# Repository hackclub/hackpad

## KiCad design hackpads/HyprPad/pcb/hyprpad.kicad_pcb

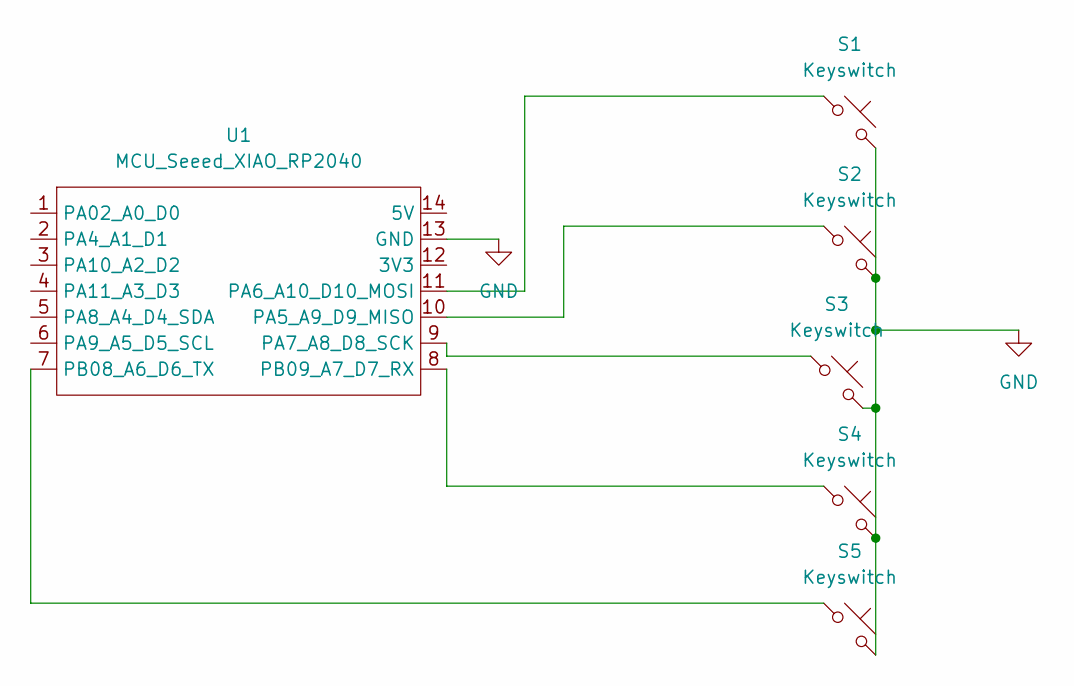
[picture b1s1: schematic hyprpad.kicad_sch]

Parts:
S1, S2, S3, S4, S5: Keyswitch; MX_PCB_1.00u
U1: MCU_Seeed_XIAO_RP2040; Seeed_XIAO_RP2040

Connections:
GND: S1.2, S2.2, S3.2, S4.2, S5.2, U1.13 (GND)
unnamed: S2.1, U1.10 (PA5_A9_D9_MISO)
unnamed: S1.1, U1.11 (PA6_A10_D10_MOSI)
unnamed: S3.1, U1.9 (PA7_A8_D8_SCK)
unnamed: S5.1, U1.7 (PB08_A6_D6_TX)
unnamed: S4.1, U1.8 (PB09_A7_D7_RX)

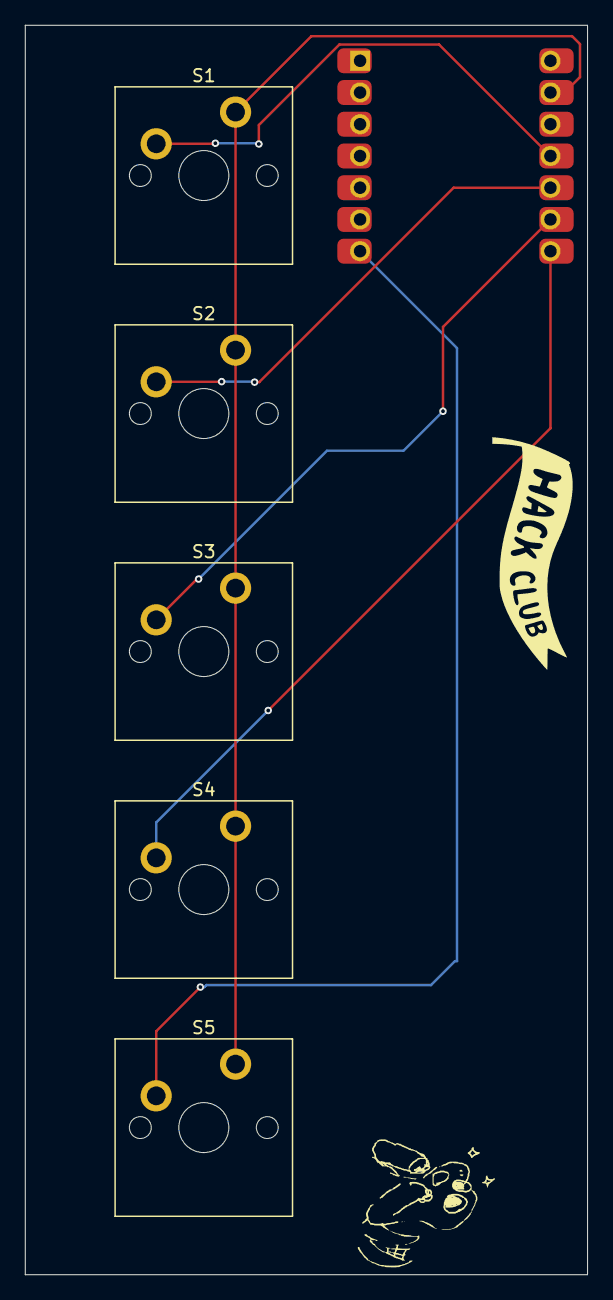
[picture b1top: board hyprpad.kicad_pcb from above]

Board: 2 copper layers, 45.0 x 100.0 mm, 6 parts (0 on the bottom side), 6 nets.

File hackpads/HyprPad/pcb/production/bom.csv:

Designator,Footprint,Quantity,Value,LCSC Part #
"S1, S2, S3, S4, S5",MX_PCB_1.00u,5,Keyswitch,
U1,Seeed_XIAO_RP2040,1,MCU_Seeed_XIAO_RP2040,

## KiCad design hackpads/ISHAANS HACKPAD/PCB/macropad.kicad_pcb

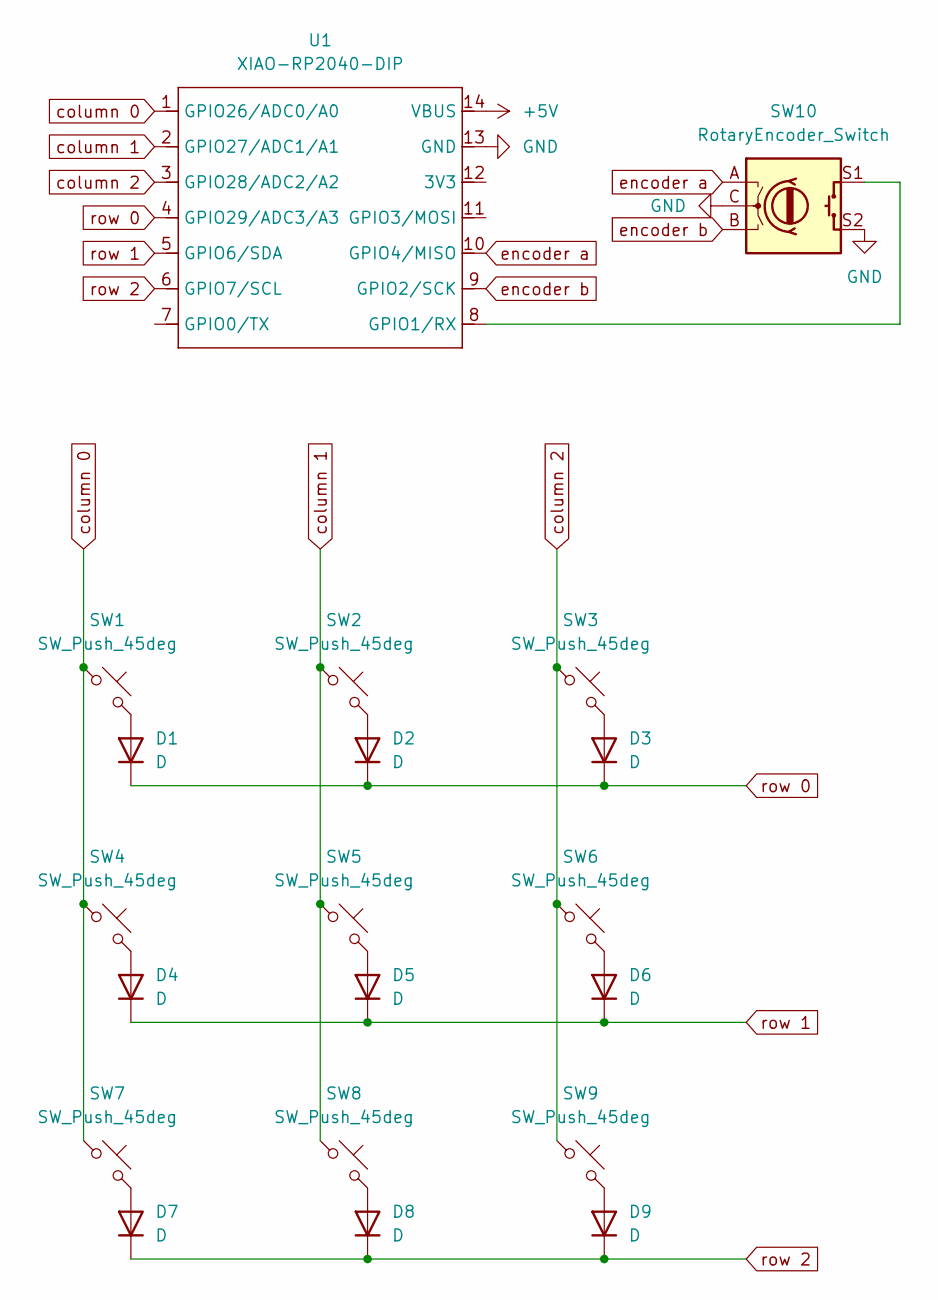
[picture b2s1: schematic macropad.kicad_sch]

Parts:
D1, D2, D3, D4, D5, D6, D7, D8, D9: D; LED_SK6812MINI_PLCC4_3.5x3.5mm_P1.75mm
SW1, SW2, SW3, SW4, SW5, SW6, SW7, SW8, SW9: SW_Push_45deg; SW_Cherry_MX_1.00u_PCB
SW10: RotaryEncoder_Switch; RotaryEncoder_Alps_EC11E-Switch_Vertical_H20mm_CircularMoun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
U1: XIAO-RP2040-DIP

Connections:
+5V: U1.14 (VBUS)
GND: SW10.C, SW10.S2, U1.13 (GND)
unnamed: D1.2 (A), SW1.2
unnamed: D2.2 (A), SW2.2
unnamed: D3.2 (A), SW3.2
unnamed: D4.2 (A), SW4.2
unnamed: D5.2 (A), SW5.2
unnamed: D6.2 (A), SW6.2
unnamed: D7.2 (A), SW7.2
unnamed: D8.2 (A), SW8.2
unnamed: D9.2 (A), SW9.2
unnamed: SW10.S1, U1.8 (GPIO1/RX)
column 0: SW1.1, SW4.1, SW7.1, U1.1 (GPIO26/ADC0/A0)
column 1: SW2.1, SW5.1, SW8.1, U1.2 (GPIO27/ADC1/A1)
column 2: SW3.1, SW6.1, SW9.1, U1.3 (GPIO28/ADC2/A2)
encoder a: SW10.A, U1.10 (GPIO4/MISO)
encoder b: SW10.B, U1.9 (GPIO2/SCK)
row 0: D1.1 (K), D2.1 (K), D3.1 (K), U1.4 (GPIO29/ADC3/A3)
row 1: D4.1 (K), D5.1 (K), D6.1 (K), U1.5 (GPIO6/SDA)
row 2: D7.1 (K), D8.1 (K), D9.1 (K), U1.6 (GPIO7/SCL)

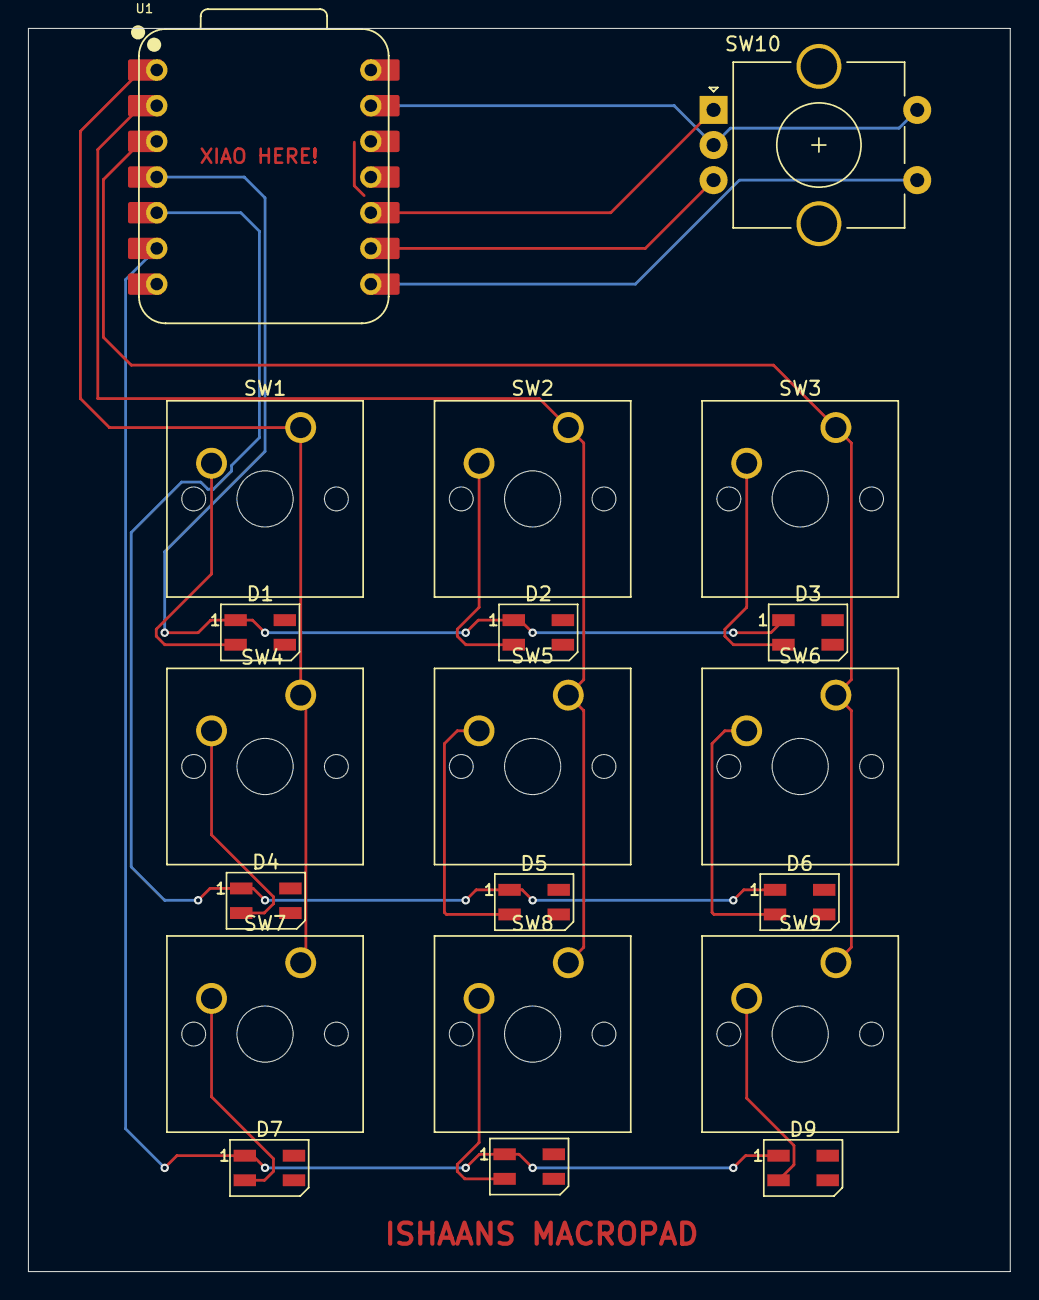
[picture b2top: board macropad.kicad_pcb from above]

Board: 2 copper layers, 69.9 x 88.5 mm, 20 parts (0 on the bottom side), 19 nets.

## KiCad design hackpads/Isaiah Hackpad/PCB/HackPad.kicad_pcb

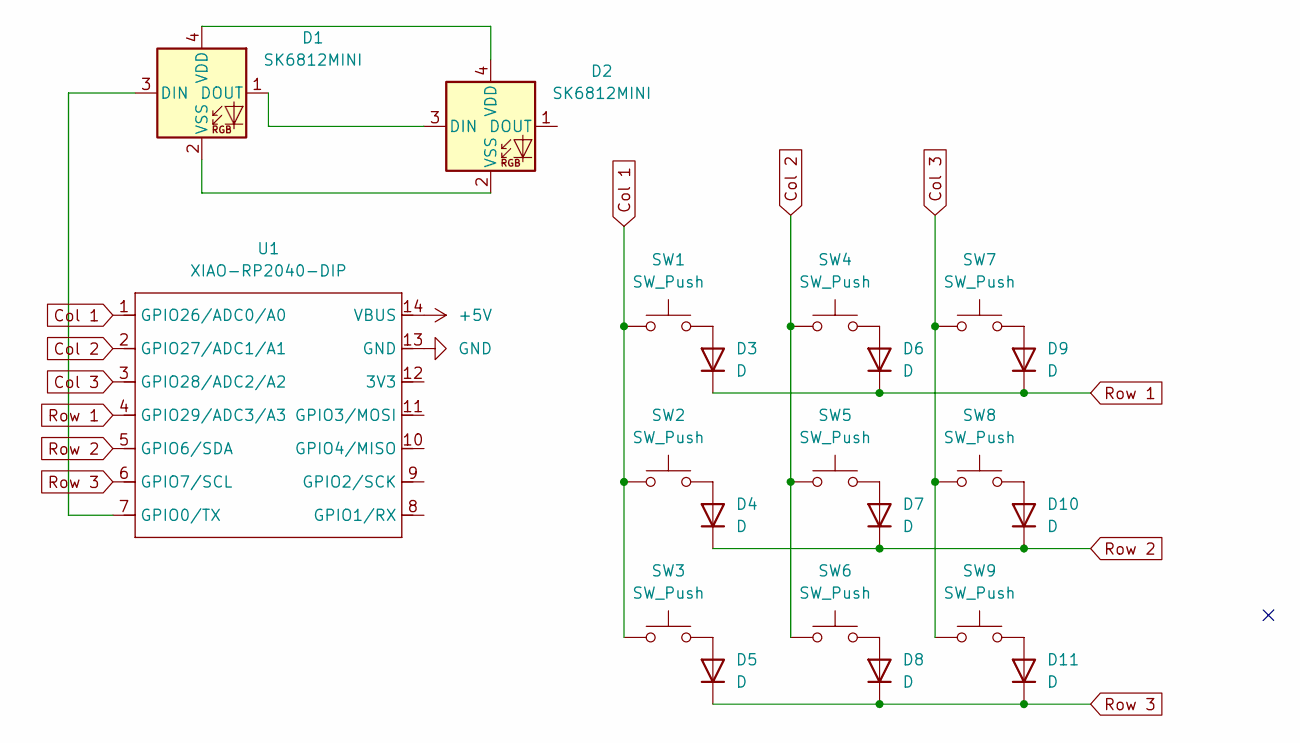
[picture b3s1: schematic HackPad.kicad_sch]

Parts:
D1, D2: SK6812MINI; LED_SK6812MINI_PLCC4_3.5x3.5mm_P1.75mm
D3, D4, D5, D6, D7, D8, D9, D10, D11: D; D_DO-35_SOD27_P7.62mm_Horizontal
SW1, SW2, SW3, SW4, SW5, SW6, SW7, SW8, SW9: SW_Push; SW_Cherry_MX_1.00u_PCB
U1: XIAO-RP2040-DIP

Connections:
+5V: U1.14 (VBUS)
Col 1: SW1.1, SW2.1, SW3.1, U1.1 (GPIO26/ADC0/A0)
Col 2: SW4.1, SW5.1, SW6.1, U1.2 (GPIO27/ADC1/A1)
Col 3: SW7.1, SW8.1, SW9.1, U1.3 (GPIO28/ADC2/A2)
GND: U1.13 (GND)
unnamed: D1.3 (DIN), U1.7 (GPIO0/TX)
unnamed: D1.1 (DOUT), D2.3 (DIN)
unnamed: D1.4 (VDD), D2.4 (VDD)
unnamed: D1.2 (VSS), D2.2 (VSS)
unnamed: D3.2 (A), SW1.2
unnamed: D4.2 (A), SW2.2
unnamed: D5.2 (A), SW3.2
unnamed: D6.2 (A), SW4.2
unnamed: D7.2 (A), SW5.2
unnamed: D8.2 (A), SW6.2
unnamed: D9.2 (A), SW7.2
unnamed: D10.2 (A), SW8.2
unnamed: D11.2 (A), SW9.2
Row 1: D3.1 (K), D6.1 (K), D9.1 (K), U1.4 (GPIO29/ADC3/A3)
Row 2: D4.1 (K), D7.1 (K), D10.1 (K), U1.5 (GPIO6/SDA)
Row 3: D5.1 (K), D8.1 (K), D11.1 (K), U1.6 (GPIO7/SCL)

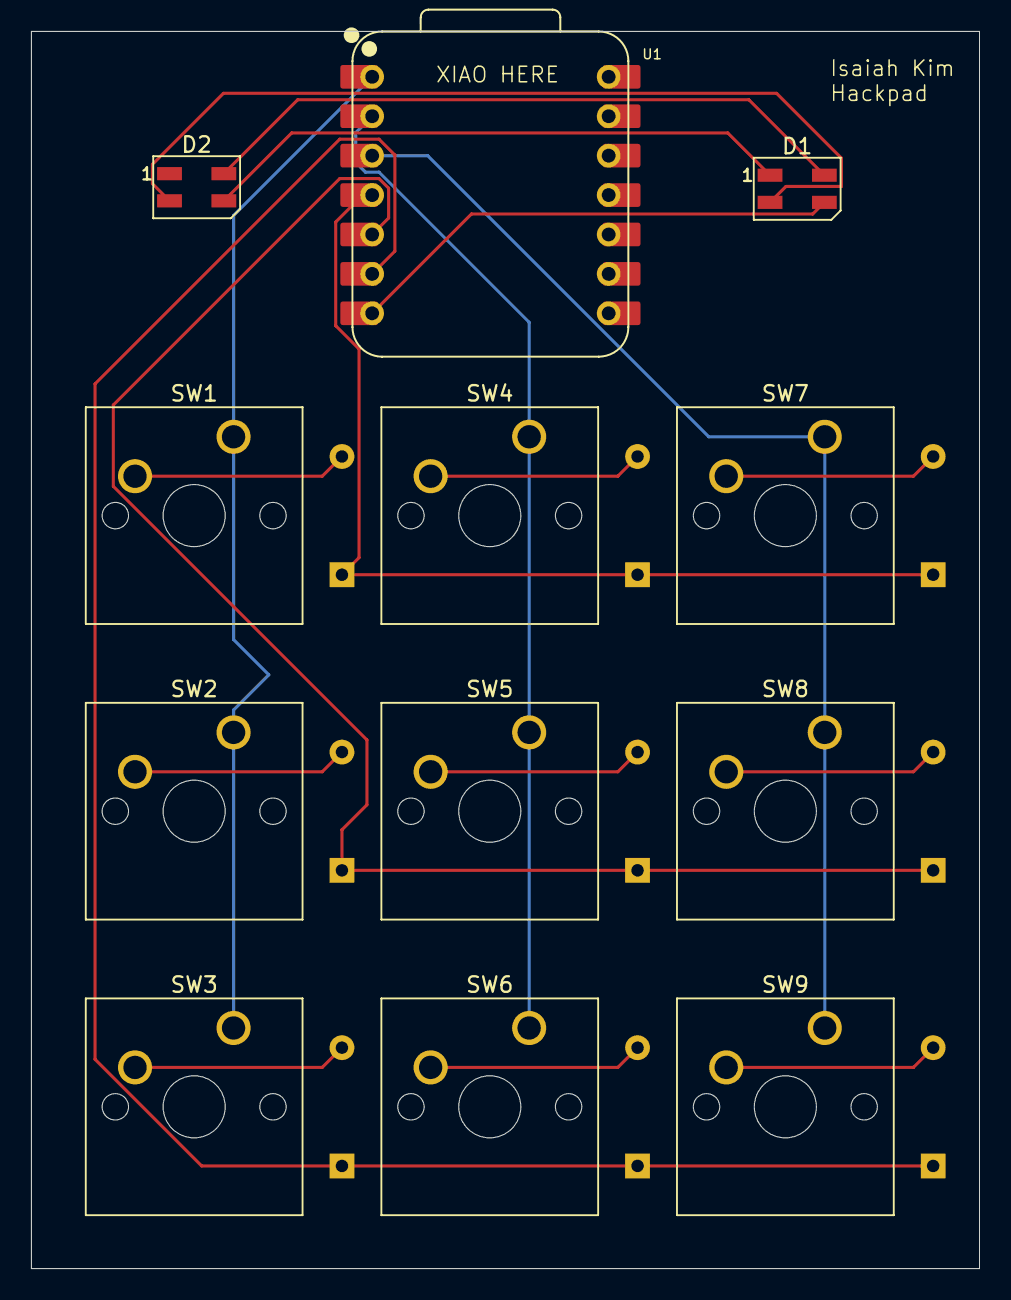
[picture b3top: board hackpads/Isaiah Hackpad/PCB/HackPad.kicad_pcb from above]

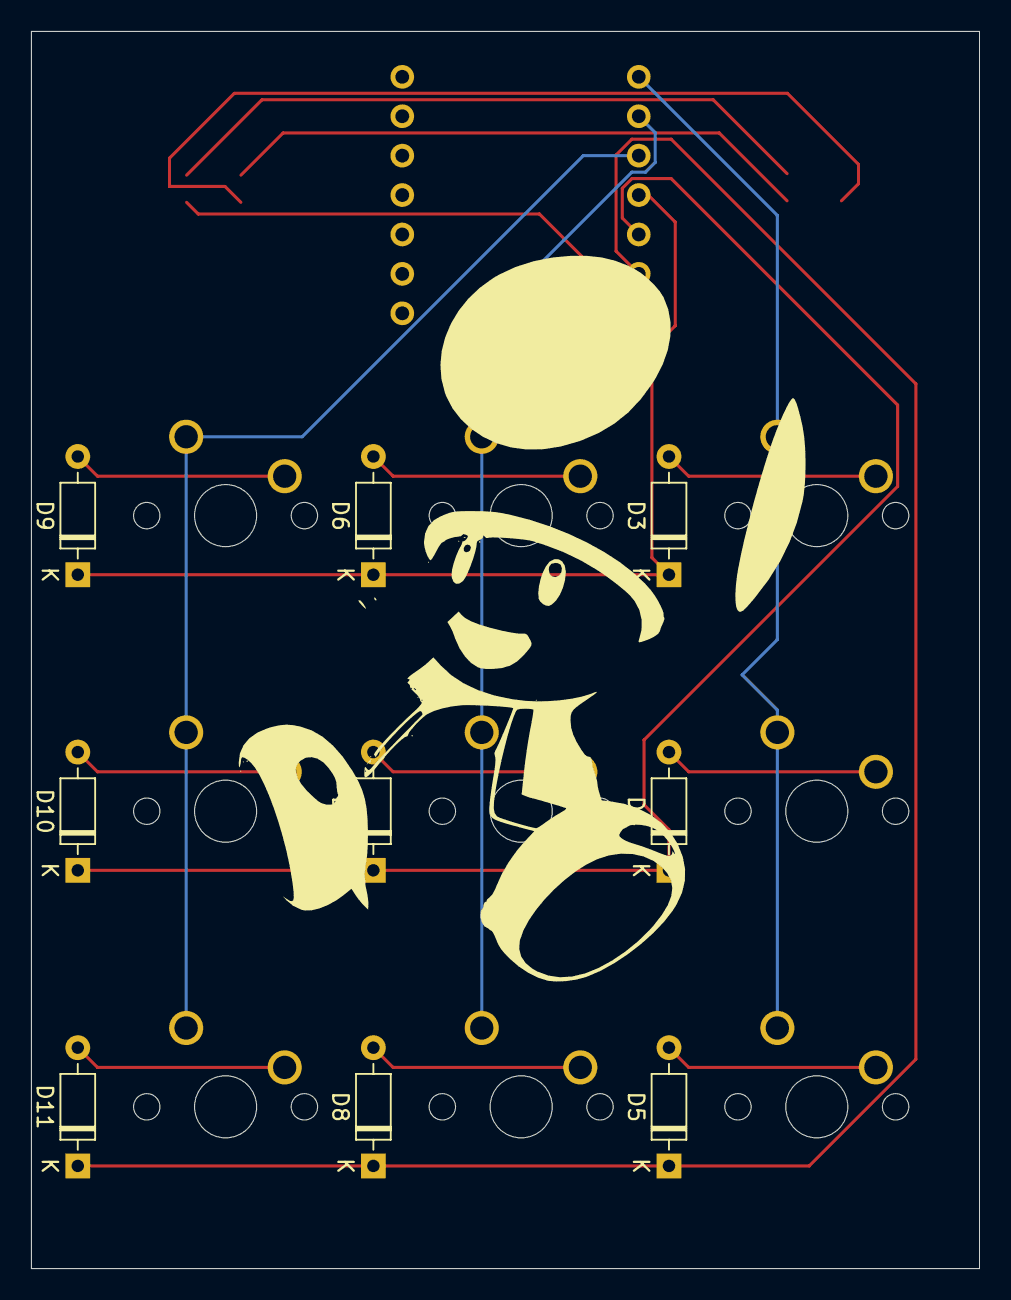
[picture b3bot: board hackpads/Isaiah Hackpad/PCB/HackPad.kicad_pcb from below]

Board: 2 copper layers, 61.1 x 79.7 mm, 21 parts (9 on the bottom side), 19 nets.

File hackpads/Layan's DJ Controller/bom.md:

# Hackpad - Bill of Materials

- 1x XIAO SEEED RP2040: XIAO-RP2040-DIP
- 1x MCP23017-SO: Package_SO:SOIC-28W_7.5x17.9mm_P1.27mm
- 2x LEDs: LED_SK6812MINI_PLCC4_3.5x3.5mm_P1.75mm
- 2x Bourns slide potentiometer: TRIM_PTA4543-2015DPA103
- 2x 4.7kΩ resistors: R_Axial_DIN0204_L3.6mm_D1.6mm_P7.62mm_Horizontal
- 8x Cherry MX switches: SW_Cherry_MX_1.00u_PCB
- 2x Alps rotary encoders: RotaryEncoder_Alps_EC11E_Vertical_H20mm

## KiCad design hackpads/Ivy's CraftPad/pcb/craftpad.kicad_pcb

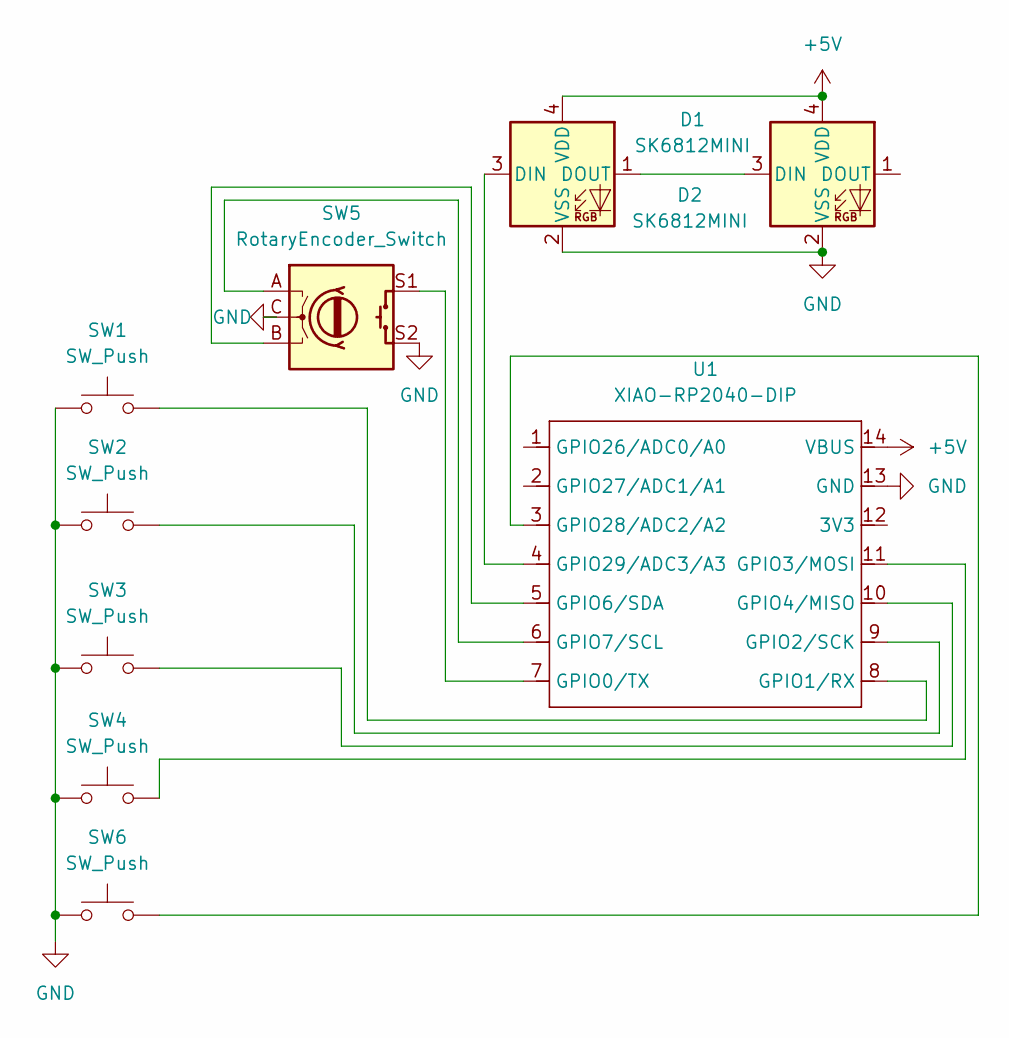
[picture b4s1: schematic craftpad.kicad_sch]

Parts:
D1, D2: SK6812MINI; LED_SK6812MINI_PLCC4_3.5x3.5mm_P1.75mm
SW1, SW2, SW3, SW4, SW6: SW_Push; SW_Cherry_MX_1.00u_PCB
SW5: RotaryEncoder_Switch; RotaryEncoder_Alps_EC11E-Switch_Vertical_H20mm_CircularMoun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
U1: XIAO-RP2040-DIP

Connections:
+5V: D1.4 (VDD), D2.4 (VDD), U1.14 (VBUS)
GND: D1.2 (VSS), D2.2 (VSS), SW1.1, SW2.1, SW3.1, SW4.1, SW5.C, SW5.S2, SW6.1, U1.13 (GND)
unnamed: D1.3 (DIN), U1.4 (GPIO29/ADC3/A3)
unnamed: D1.1 (DOUT), D2.3 (DIN)
unnamed: SW5.S1, U1.7 (GPIO0/TX)
unnamed: SW1.2, U1.8 (GPIO1/RX)
unnamed: SW2.2, U1.9 (GPIO2/SCK)
unnamed: SW4.2, U1.11 (GPIO3/MOSI)
unnamed: SW3.2, U1.10 (GPIO4/MISO)
unnamed: SW5.B, U1.5 (GPIO6/SDA)
unnamed: SW5.A, U1.6 (GPIO7/SCL)
unnamed: SW6.2, U1.3 (GPIO28/ADC2/A2)

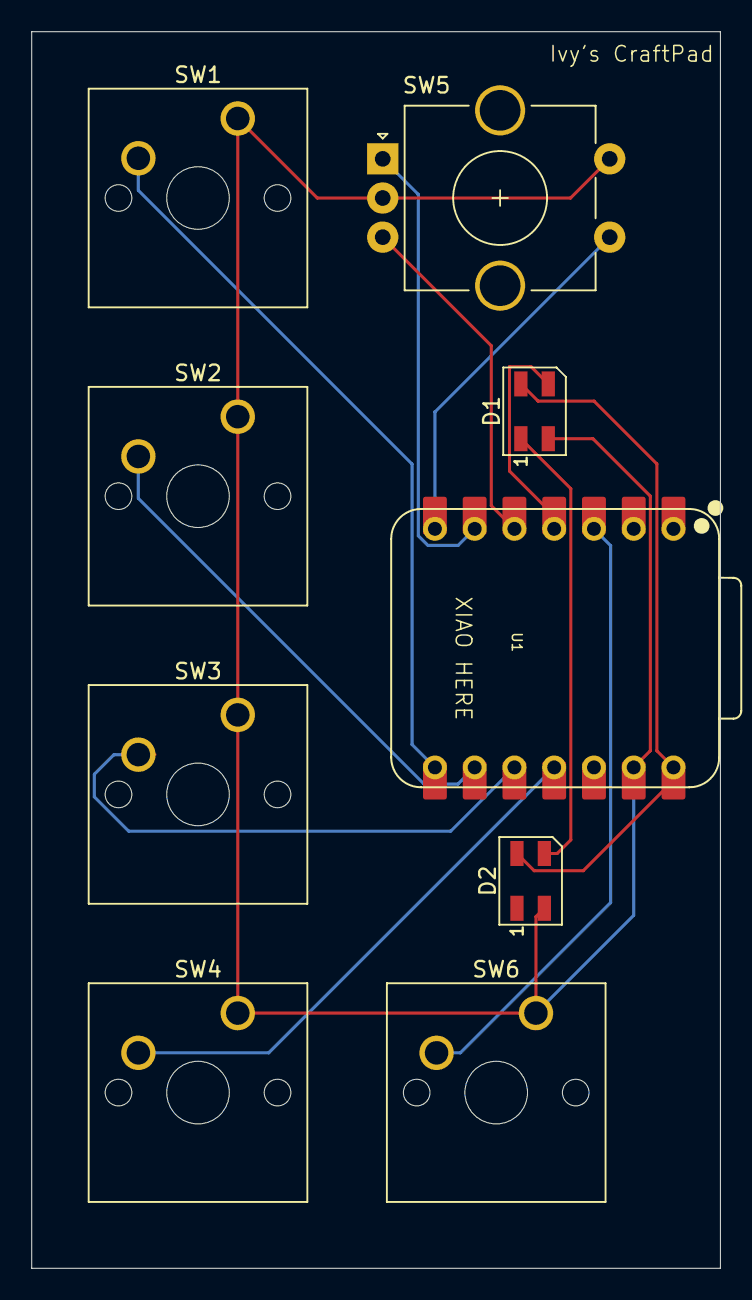
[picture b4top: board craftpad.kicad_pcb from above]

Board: 2 copper layers, 44.0 x 79.0 mm, 9 parts (0 on the bottom side), 12 nets.

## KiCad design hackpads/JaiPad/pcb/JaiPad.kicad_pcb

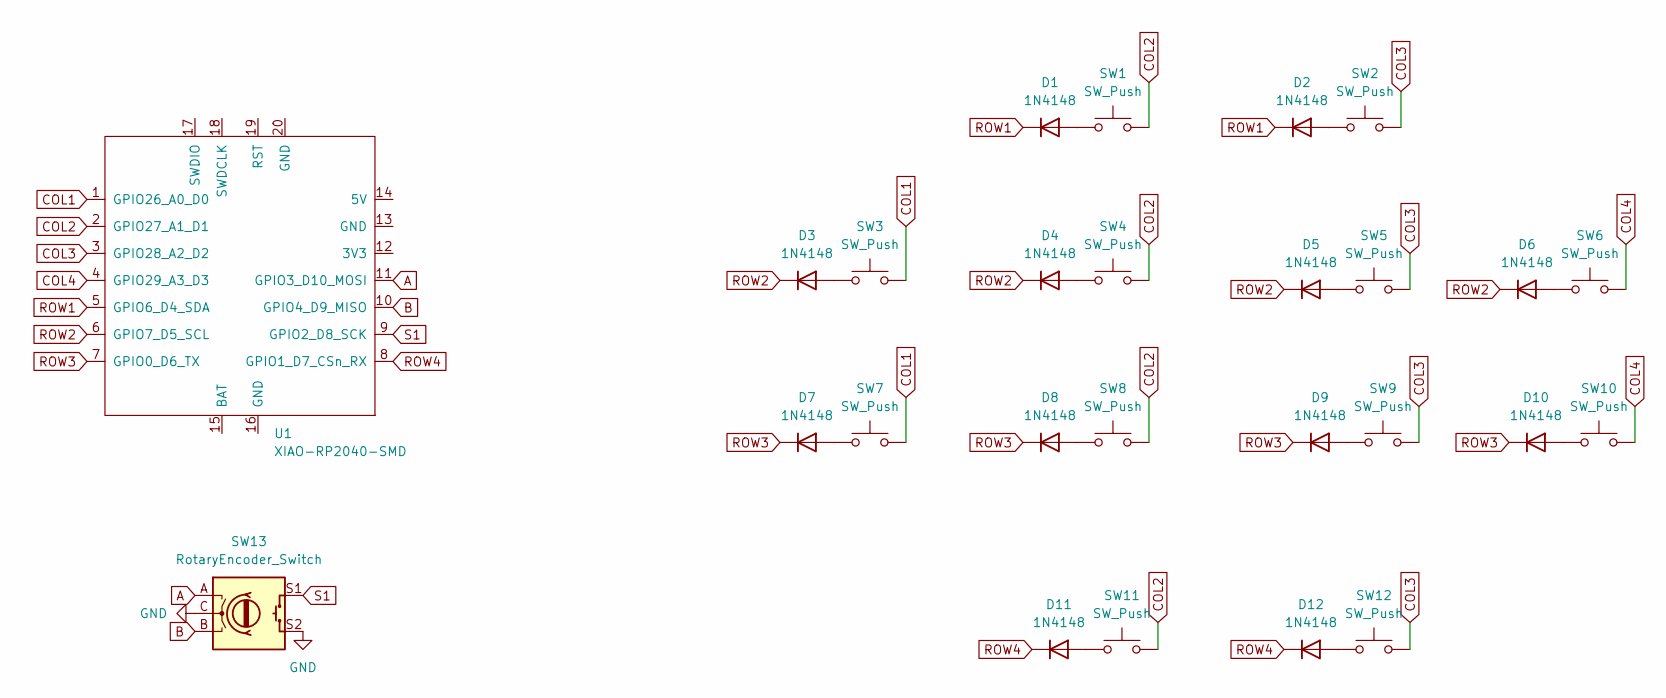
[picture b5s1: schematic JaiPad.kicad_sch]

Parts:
D1, D2, D3, D4, D5, D6, D7, D8, D9, D10, D11, D12: 1N4148; D_DO-35_SOD27_P7.62mm_Horizontal
SW1, SW2, SW3, SW4, SW5, SW6, SW7, SW8, SW9, SW10, SW11, SW12: SW_Push; SW_Kailh_Choc_V2_1.00u
SW13: RotaryEncoder_Switch; RotaryEncoder_Alps_EC11E-Switch_Vertical_H20mm_CircularMoun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
U1: XIAO-RP2040-SMD; XIAO-RP2040-DIP

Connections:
A: SW13.A, U1.11 (GPIO3_D10_MOSI)
B: SW13.B, U1.10 (GPIO4_D9_MISO)
COL1: SW3.2, SW7.2, U1.1 (GPIO26_A0_D0)
COL2: SW1.2, SW4.2, SW8.2, SW11.2, U1.2 (GPIO27_A1_D1)
COL3: SW2.2, SW5.2, SW9.2, SW12.2, U1.3 (GPIO28_A2_D2)
COL4: SW6.2, SW10.2, U1.4 (GPIO29_A3_D3)
GND: SW13.C, SW13.S2
unnamed: D1.2 (A), SW1.1
unnamed: D2.2 (A), SW2.1
unnamed: D3.2 (A), SW3.1
unnamed: D4.2 (A), SW4.1
unnamed: D5.2 (A), SW5.1
unnamed: D6.2 (A), SW6.1
unnamed: D7.2 (A), SW7.1
unnamed: D8.2 (A), SW8.1
unnamed: D9.2 (A), SW9.1
unnamed: D10.2 (A), SW10.1
unnamed: D11.2 (A), SW11.1
unnamed: D12.2 (A), SW12.1
ROW1: D1.1 (K), D2.1 (K), U1.5 (GPIO6_D4_SDA)
ROW2: D3.1 (K), D4.1 (K), D5.1 (K), D6.1 (K), U1.6 (GPIO7_D5_SCL)
ROW3: D7.1 (K), D8.1 (K), D9.1 (K), D10.1 (K), U1.7 (GPIO0_D6_TX)
ROW4: D11.1 (K), D12.1 (K), U1.8 (GPIO1_D7_CSn_RX)
S1: SW13.S1, U1.9 (GPIO2_D8_SCK)

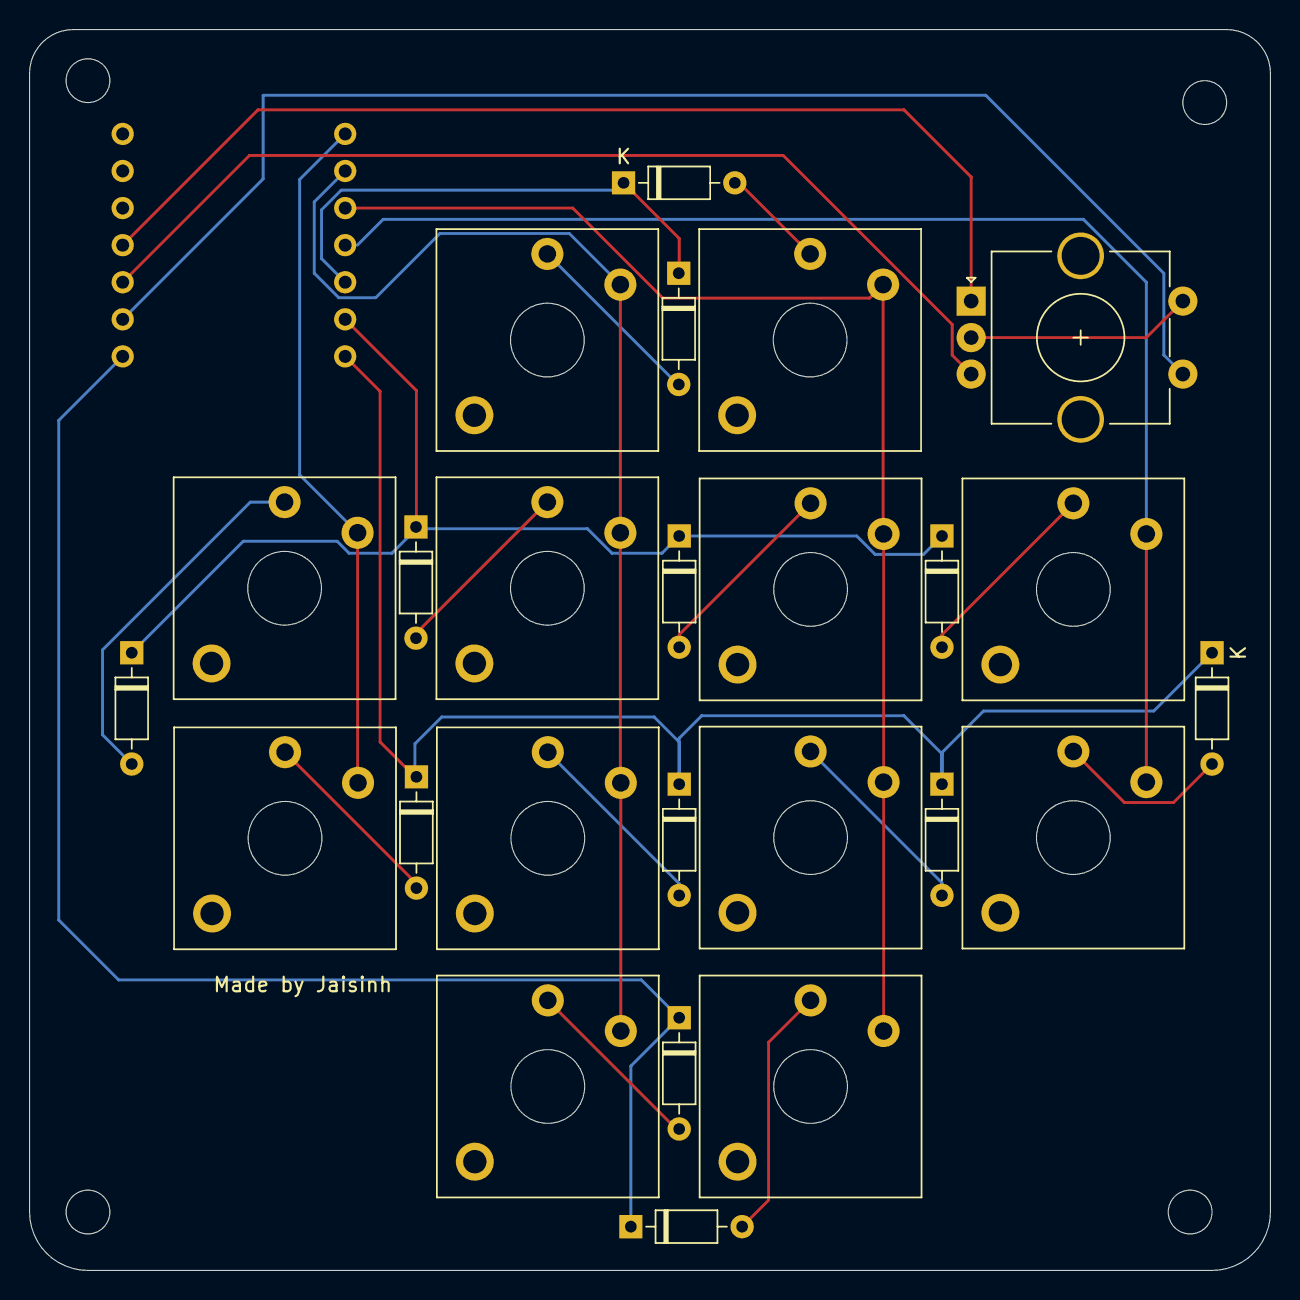
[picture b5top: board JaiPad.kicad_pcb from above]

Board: 2 copper layers, 85.0 x 85.0 mm, 26 parts (1 on the bottom side), 24 nets.

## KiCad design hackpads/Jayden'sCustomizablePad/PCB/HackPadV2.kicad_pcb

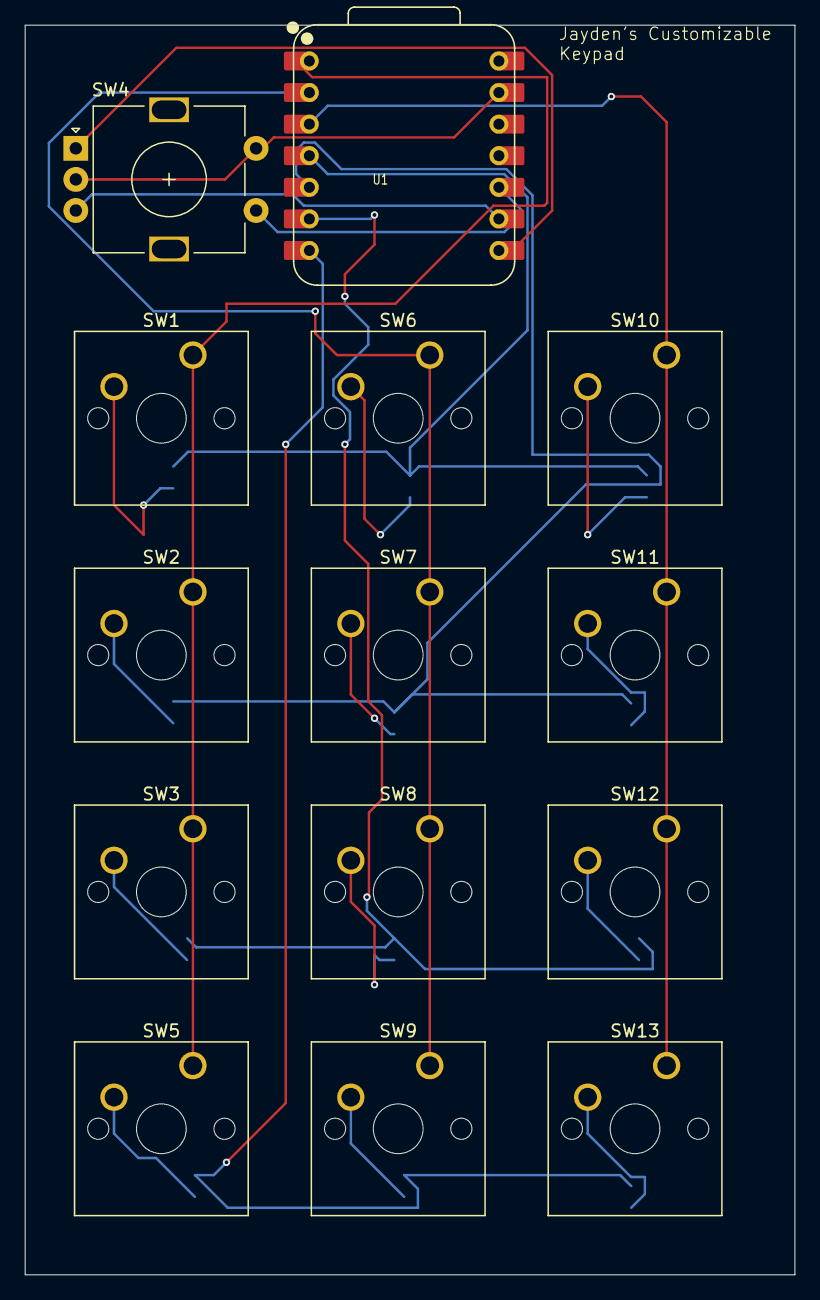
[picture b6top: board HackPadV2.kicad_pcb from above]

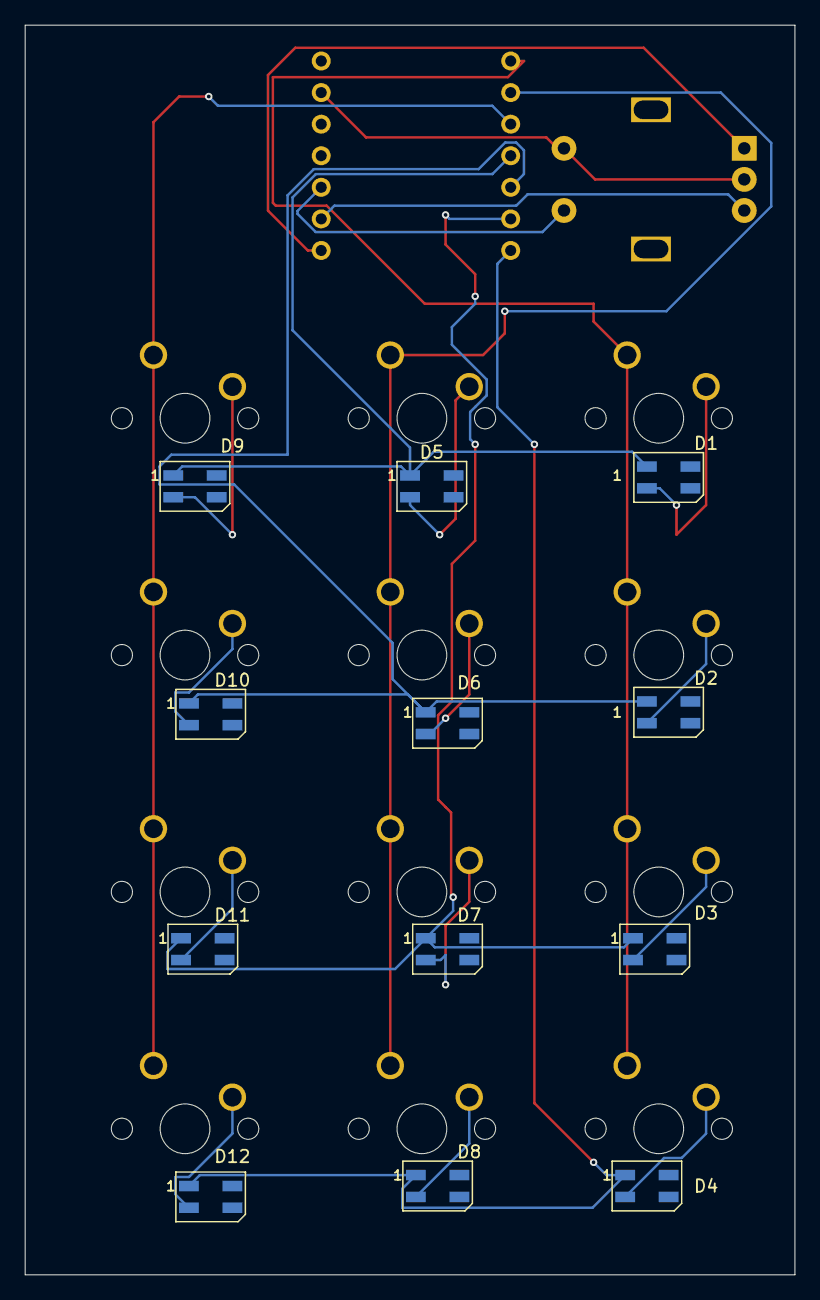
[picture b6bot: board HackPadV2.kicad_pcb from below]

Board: 2 copper layers, 61.9 x 100.5 mm, 26 parts (12 on the bottom side), 23 nets.

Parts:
D1, D2, D3, D4, D5, D6, D7, D8, D9, D10, D11, D12: D; LED_SK6812MINI_PLCC4_3.5x3.5mm_P1.75mm
SW1, SW2, SW3, SW5, SW6, SW7, SW8, SW9, SW10, SW11, SW12, SW13: SW_Push; SW_Cherry_MX_1.00u_PCB
SW4: RotaryEncoder_Switch; RotaryEncoder_Alps_EC11E-Switch_Vertical_H20mm
U1: XIAO-RP2040-DIP

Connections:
GND: SW4.C, SW4.S2, U1.13 (GND)
unnamed: D1.2 (A), SW1.2
unnamed: D2.2 (A), SW2.2
unnamed: D3.2 (A), SW3.2
unnamed: D4.2 (A), SW5.2
unnamed: D5.2 (A), SW6.2
unnamed: D6.2 (A), SW7.2
unnamed: D7.2 (A), SW8.2
unnamed: D8.2 (A), SW9.2
unnamed: D9.2 (A), SW10.2
unnamed: D10.2 (A), SW11.2
unnamed: D11.2 (A), SW12.2
unnamed: D12.2 (A), SW13.2
unnamed: SW4.A, U1.8 (GPIO1/RX)
unnamed: SW4.B, U1.9 (GPIO2/SCK)
unnamed: SW4.S1, U1.10 (GPIO4/MISO)
col1: SW1.1, SW2.1, SW3.1, SW5.1, U1.1 (GPIO26/ADC0/A0)
col2: SW6.1, SW7.1, SW8.1, SW9.1, U1.2 (GPIO27/ADC1/A1)
col3: SW10.1, SW11.1, SW12.1, SW13.1, U1.3 (GPIO28/ADC2/A2)
row1: D1.1 (K), D5.1 (K), D9.1 (K), U1.4 (GPIO29/ADC3/A3)
row2: D2.1 (K), D6.1 (K), D10.1 (K), U1.5 (GPIO6/SDA)
row3: D3.1 (K), D7.1 (K), D11.1 (K), U1.6 (GPIO7/SCL)
row4: D4.1 (K), D8.1 (K), D12.1 (K), U1.7 (GPIO0/TX)

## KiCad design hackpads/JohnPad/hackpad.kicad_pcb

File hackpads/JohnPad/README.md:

# JohnPad

# BOM:
- 12x Cherry MX switches or https://mechanicalkeyboards.com/products/gateron-jupiter-banana-59g-tactile-pcb-mount (going to ask for approval, but just wanted to write it down)
- 1x PCB
- 12x Through-hole 1N4148 Diodes
- 12x WS2812B LEDs

Would be nice to get low profile key caps 🥺

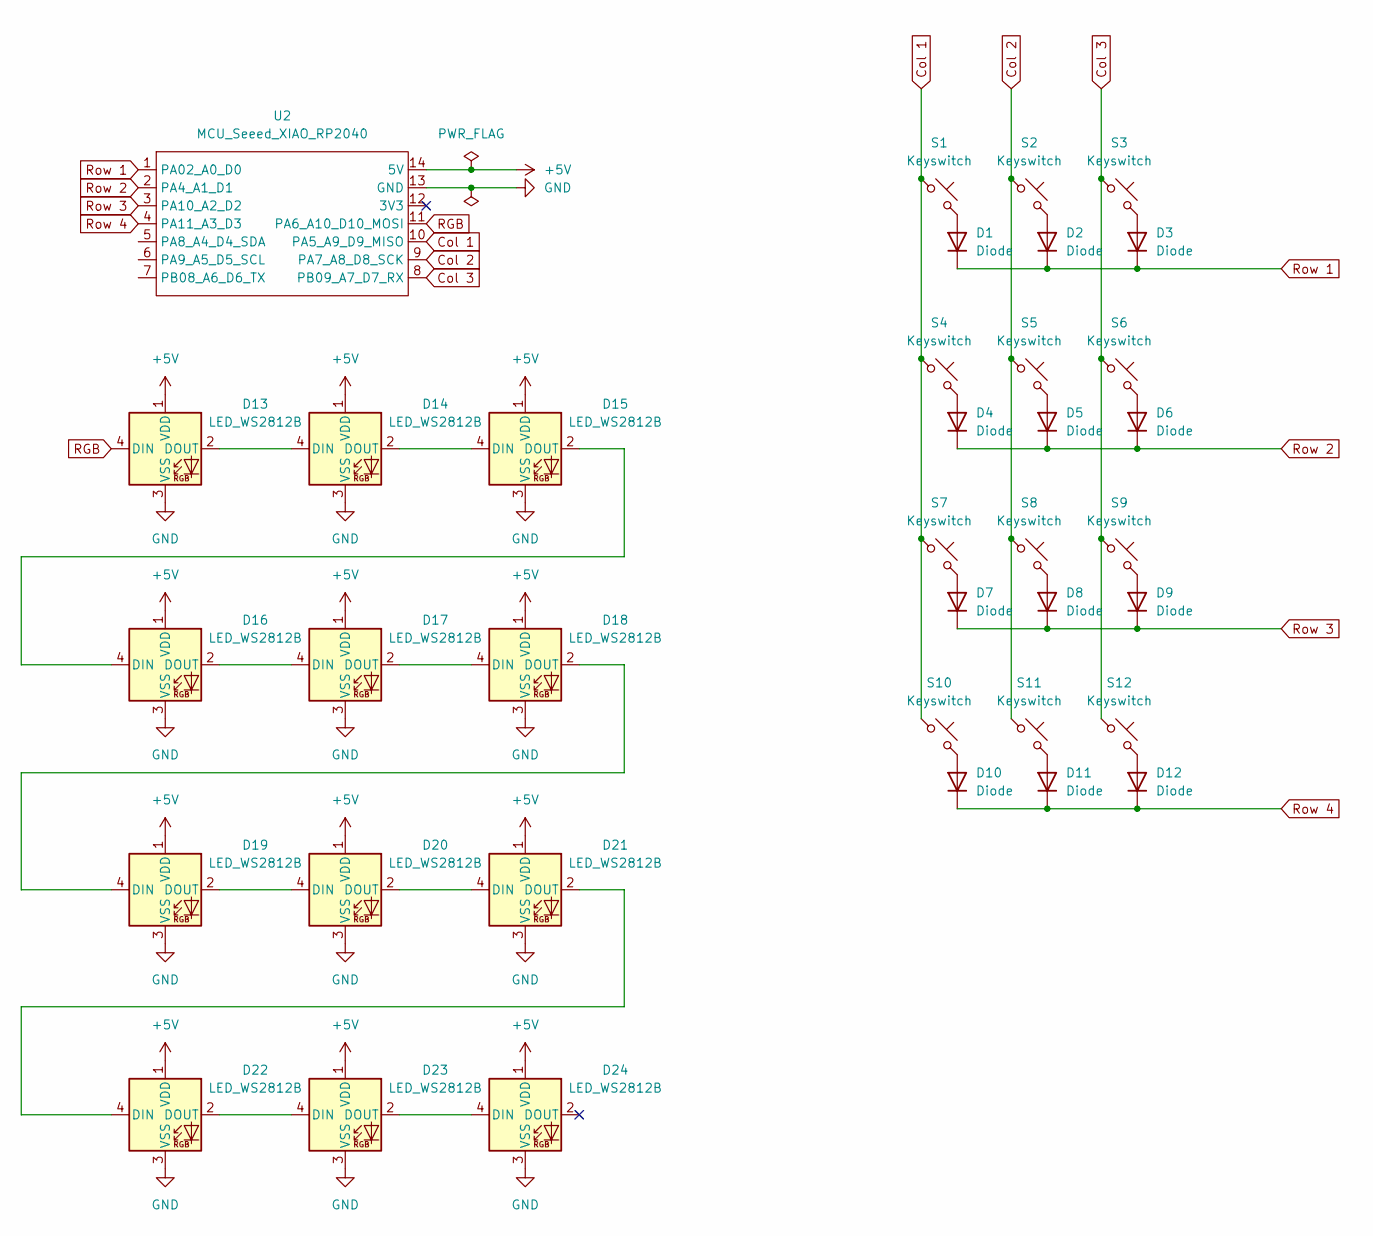
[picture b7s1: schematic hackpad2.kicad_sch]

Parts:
D1, D2, D3, D4, D5, D6, D7, D8, D9, D10, D11, D12: Diode; Diode_DO-35
D13, D14, D15, D16, D17, D18, D19, D20, D21, D22, D23, D24: LED_WS2812B
S1, S2, S3, S4, S5, S6, S7, S8, S9, S10, S11, S12: Keyswitch; MX_PCB_1.00u
U2: MCU_Seeed_XIAO_RP2040; XIAO-Generic-Thruhole-14P-2.54-21X17.8MM

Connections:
+5V: D13.1 (VDD), D14.1 (VDD), D15.1 (VDD), D16.1 (VDD), D17.1 (VDD), D18.1 (VDD), D19.1 (VDD), D20.1 (VDD), D21.1 (VDD), D22.1 (VDD), D23.1 (VDD), D24.1 (VDD), U2.14 (5V)
Col 1: S1.1, S4.1, S7.1, S10.1, U2.10 (PA5_A9_D9_MISO)
Col 2: S2.1, S5.1, S8.1, S11.1, U2.9 (PA7_A8_D8_SCK)
Col 3: S3.1, S6.1, S9.1, S12.1, U2.8 (PB09_A7_D7_RX)
GND: D13.3 (VSS), D14.3 (VSS), D15.3 (VSS), D16.3 (VSS), D17.3 (VSS), D18.3 (VSS), D19.3 (VSS), D20.3 (VSS), D21.3 (VSS), D22.3 (VSS), D23.3 (VSS), D24.3 (VSS), U2.13 (GND)
unnamed: D1.2 (A), S1.2
unnamed: D2.2 (A), S2.2
unnamed: D3.2 (A), S3.2
unnamed: D4.2 (A), S4.2
unnamed: D5.2 (A), S5.2
unnamed: D6.2 (A), S6.2
unnamed: D7.2 (A), S7.2
unnamed: D8.2 (A), S8.2
unnamed: D9.2 (A), S9.2
unnamed: D10.2 (A), S10.2
unnamed: D11.2 (A), S11.2
unnamed: D12.2 (A), S12.2
unnamed: D13.2 (DOUT), D14.4 (DIN)
unnamed: D14.2 (DOUT), D15.4 (DIN)
unnamed: D15.2 (DOUT), D16.4 (DIN)
unnamed: D16.2 (DOUT), D17.4 (DIN)
unnamed: D17.2 (DOUT), D18.4 (DIN)
unnamed: D18.2 (DOUT), D19.4 (DIN)
unnamed: D19.2 (DOUT), D20.4 (DIN)
unnamed: D20.2 (DOUT), D21.4 (DIN)
unnamed: D21.2 (DOUT), D22.4 (DIN)
unnamed: D22.2 (DOUT), D23.4 (DIN)
unnamed: D23.2 (DOUT), D24.4 (DIN)
RGB: D13.4 (DIN), U2.11 (PA6_A10_D10_MOSI)
Row 1: D1.1 (K), D2.1 (K), D3.1 (K), U2.1 (PA02_A0_D0)
Row 2: D4.1 (K), D5.1 (K), D6.1 (K), U2.2 (PA4_A1_D1)
Row 3: D7.1 (K), D8.1 (K), D9.1 (K), U2.3 (PA10_A2_D2)
Row 4: D10.1 (K), D11.1 (K), D12.1 (K), U2.4 (PA11_A3_D3)
